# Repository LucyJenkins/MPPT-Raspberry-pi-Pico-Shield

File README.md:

# MPPT-Raspberry-pi-Pico-Shield
A small project implementing a Maximum Power Point Tracker using the format of Raspberry pi Pico Shield

# References:
1. https://fr.scribd.com/document/404356941/Regulated-Output-Voltage-Double-Switch-Buck-Boost-Converter-for-Photovoltaic-Energy-Application 
2. https://www.engr.colostate.edu/ECE562/98lectures/l09.pdf

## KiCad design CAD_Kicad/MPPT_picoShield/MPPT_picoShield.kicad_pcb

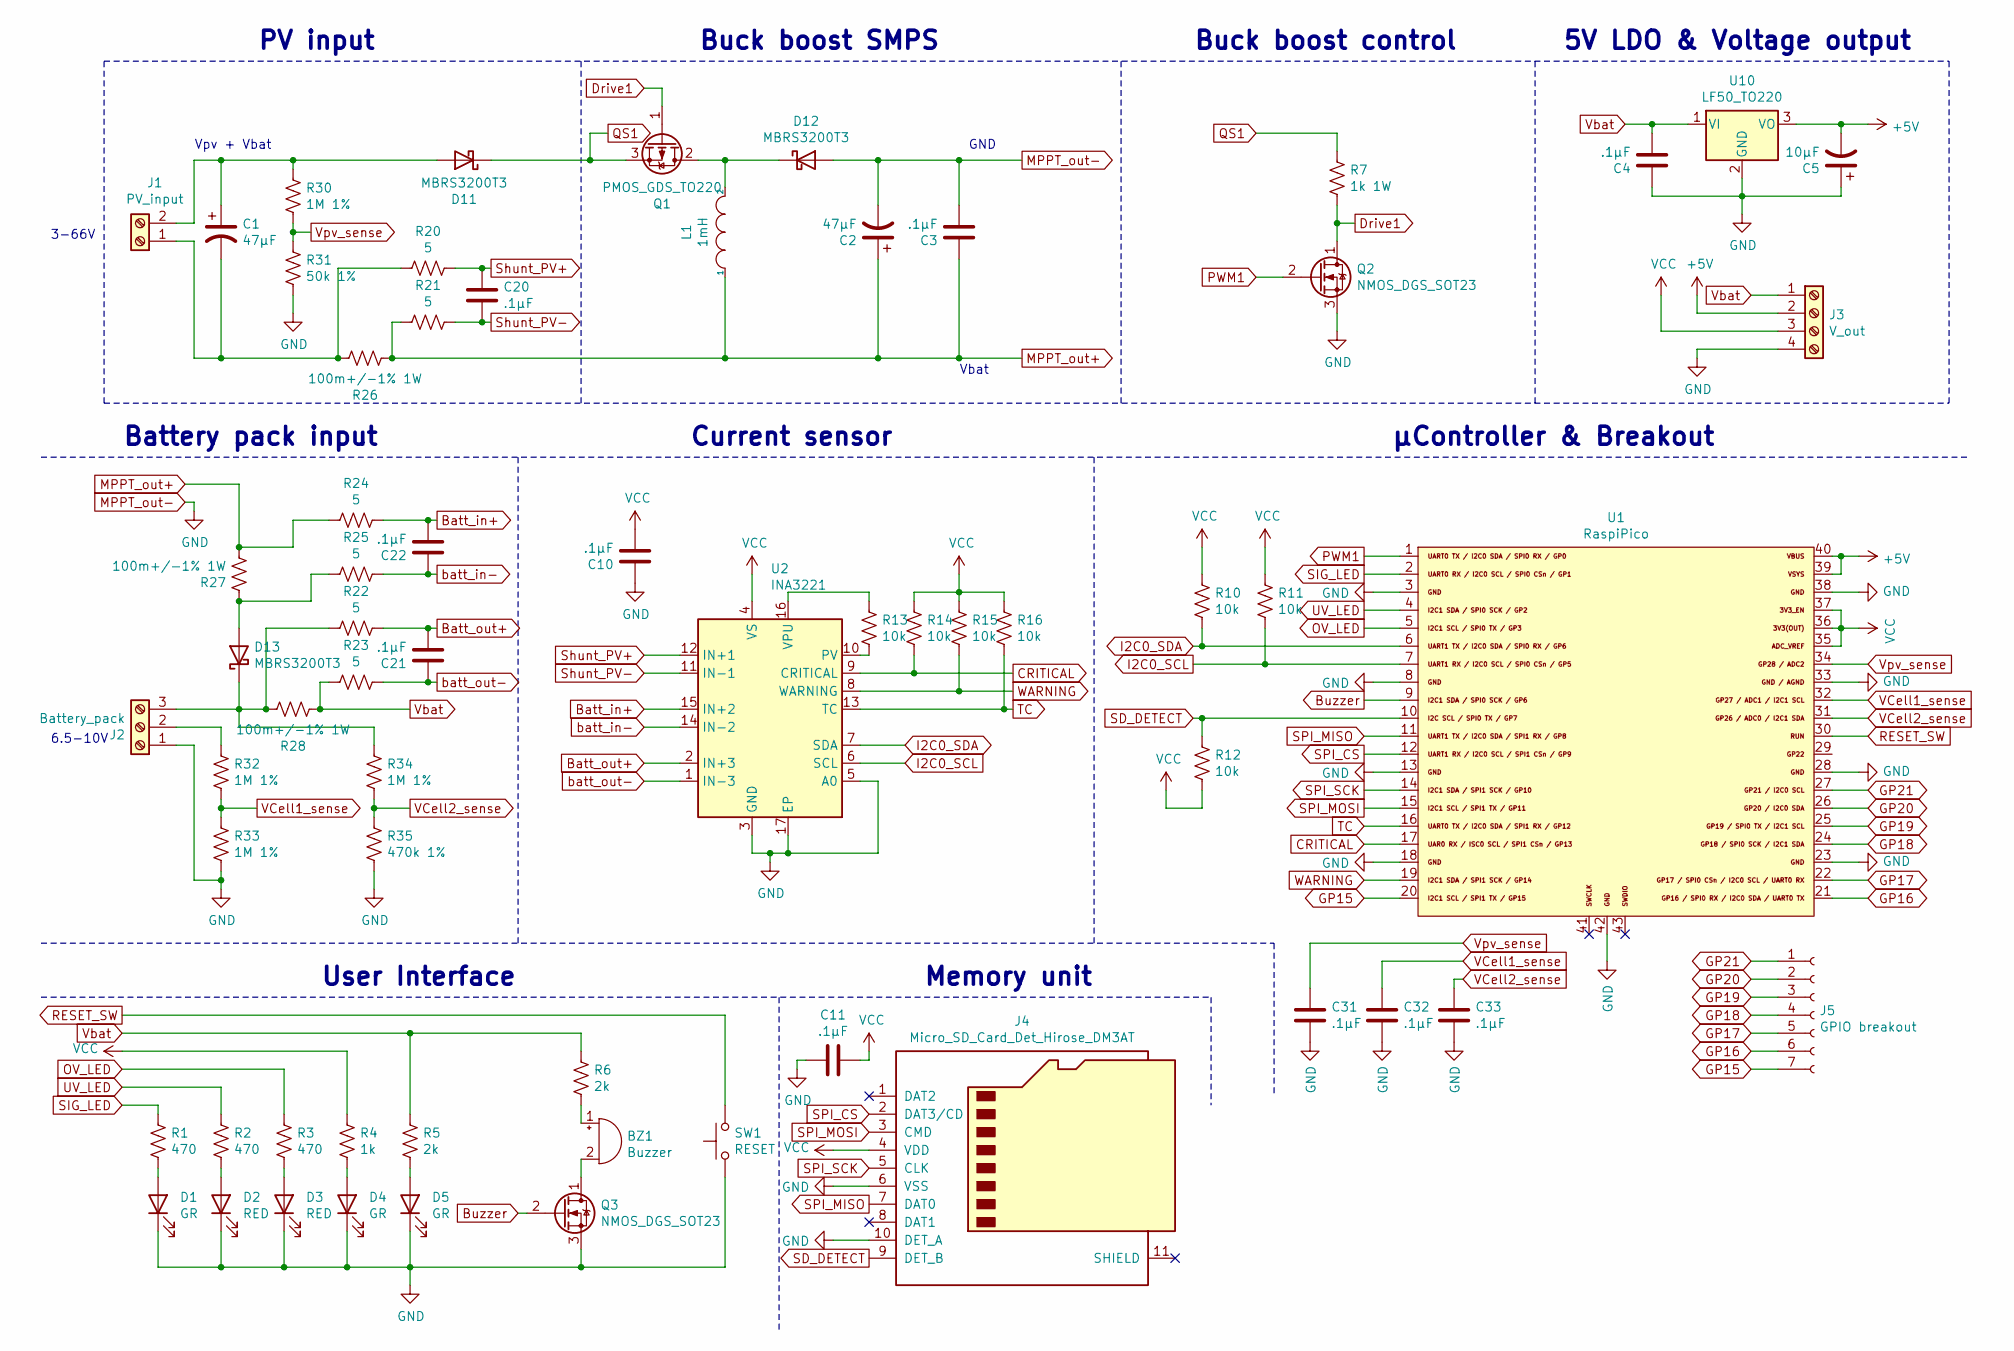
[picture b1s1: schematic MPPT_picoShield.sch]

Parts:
BZ1: Buzzer; PKM13EPYH4002-B0
C1, C2: 47µF; CP_Radial_D10.0mm_P5.00mm
C3, C4, C10, C11, C20, C21, C22, C31, C32, C33: .1µF; C_0603_1608Metric
C5: 10µF; CP_Radial_D10.0mm_P5.00mm
D1, D4, D5: GR; LED_0805_2012Metric
D2, D3: RED; LED_0805_2012Metric
D11, D12, D13: MBRS3200T3; MBRS3200T3G
J1: PV_input; TerminalBlock_bornier-2_P5.08mm
J2: Battery_pack; TerminalBlock_bornier-3_P5.08mm
J3: V_out; TerminalBlock_bornier-4_P5.08mm
J4: Micro_SD_Card_Det_Hirose_DM3AT; DM3ATSFPEJM5
J5: GPIO breakout; PinHeader_1x07_P2.54mm_Vertical
L1: 1mH; PA4320.105NLT
Q1: PMOS_GDS_TO220; TO-220-3_Vertical
Q2, Q3: NMOS_DGS_SOT23; SOT-23
R1, R2, R3: 470; R_0603_1608Metric
R4: 1k; R_0603_1608Metric
R5, R6: 2k; R_0603_1608Metric
R7: 1k 1W; R_1206_3216Metric
R10, R11, R12, R13, R14, R15, R16: 10k; R_0603_1608Metric
R20, R21, R22, R23, R24, R25: 5; R_0603_1608Metric
R26, R27, R28: 100m+/-1% 1W; R_1206_3216Metric
R30, R32, R33, R34: 1M 1%; R_0603_1608Metric
R31: 50k 1%; R_0603_1608Metric
R35: 470k 1%; R_0603_1608Metric
SW1: RESET; SW_PUSH_6mm
U1: RaspiPico
U2: INA3221; Texas_RGV_S-PVQFN-N16_EP2.1x2.1mm
U10: LF50_TO220; TO-220-3_Vertical

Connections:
+5V: C5.2, J3.2, U1.39, U1.40, U10.3 (VO)
Batt_in+: C22.2, R24.1, U2.15 (IN+2)
Batt_out+: C21.2, R22.1, U2.2 (IN+3)
Buzzer: Q3.2 (G), U1.9
CRITICAL: R14.2, U1.17, U2.9 (CRITICAL)
Drive1: Q1.1 (G), Q2.1 (D), R7.2
GP15: J5.7, U1.20
GP16: J5.6, U1.21
GP17: J5.5, U1.22
GP18: J5.4, U1.24
GP19: J5.3, U1.25
GP20: J5.2, U1.26
GP21: J5.1, U1.27
I2C0_SCL: R11.2, U1.7, U2.6 (SCL)
I2C0_SDA: R10.2, U1.6, U2.7 (SDA)
MPPT_out+: C2.1, C3.1, L1.1, R21.2, R24.2, R26.2, R27.2; also elsewhere on the board
MPPT_out-: C2.2, C3.2, C4.1, C5.1, C10.1, C11.2, C31.2, C32.2, C33.2, D1.1 (K), D2.1 (K), D3.1 (K), D4.1 (K), D5.1 (K), D12.2 (A), J2.1, J3.4, J4.6 (VSS), J4.10 (DET_A), Q2.3 (S), Q3.3 (S), R31.2, R33.2, R35.2, SW1.1, U1.3, U1.8, U1.13, U1.18, U1.23, U1.28, U1.33, U1.38, U1.42, U2.3 (GND), U2.5 (A0), U2.17 (EP), U10.2 (GND); also elsewhere on the board
unnamed: BZ1.1 (-), R6.2
unnamed: BZ1.2 (+), Q3.1 (D)
unnamed 19: C1.1, D11.2 (A), J1.2, R30.1; also elsewhere on the board
unnamed 20: C1.2, J1.1, R20.2, R26.1; also elsewhere on the board
unnamed: D1.2 (A), R1.2
unnamed: D2.2 (A), R2.2
unnamed: D3.2 (A), R3.2
unnamed: D4.2 (A), R4.2
unnamed: D5.2 (A), R5.2
unnamed 26: D12.1 (K), L1.2, Q1.2 (D); also elsewhere on the board
unnamed: D13.1 (K), J2.3, R22.2, R28.1, R34.1
unnamed: D13.2 (A), R25.2, R27.1
unnamed: J2.2, R32.1
unnamed: R13.1, U2.16 (VPU)
unnamed: R13.2, U2.10 (PV)
OV_LED: R3.1, U1.5
PWM1: Q2.2 (G), U1.1
QS1: D11.1 (K), Q1.3 (S), R7.1
RESET_SW: SW1.2, U1.30
SD_DETECT: J4.9 (DET_B), R12.1, U1.10
SIG_LED: R1.1, U1.2
SPI_CS: J4.2 (DAT3/CD), U1.12
SPI_MISO: J4.7 (DAT0), U1.11
SPI_MOSI: J4.3 (CMD), U1.15
SPI_SCK: J4.5 (CLK), U1.14
Shunt_PV+: C20.1, R20.1, U2.12 (IN+1)
Shunt_PV-: C20.2, R21.1, U2.11 (IN-1)
TC: R16.2, U1.16, U2.13 (TC)
UV_LED: R2.1, U1.4
VCC: C10.2, C11.1, J3.3, J4.4 (VDD), R4.1, R10.1, R11.1, R12.2, R14.1, R15.1, R16.1, U1.35, U1.36, U1.37, U2.4 (VS); also elsewhere on the board
VCell1_sense: C32.1, R32.2, R33.1, U1.32
VCell2_sense: C33.1, R34.2, R35.1, U1.31
Vbat: C4.2, J3.1, R5.1, R6.1, R23.2, R28.2, U10.1 (VI); also elsewhere on the board
Vpv_sense: C31.1, R30.2, R31.1, U1.34
WARNING: R15.2, U1.19, U2.8 (WARNING)
batt_in-: C22.1, R25.1, U2.14 (IN-2)
batt_out-: C21.1, R23.1, U2.1 (IN-3)

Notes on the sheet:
Vpv + Vbat
Vbat
GND
Buck boost SMPS
PV input
Battery pack input
Buck boost control
µController & Breakout
User Interface
Memory unit
5V LDO & Voltage output
Current sensor
3-66V
6.5-10V

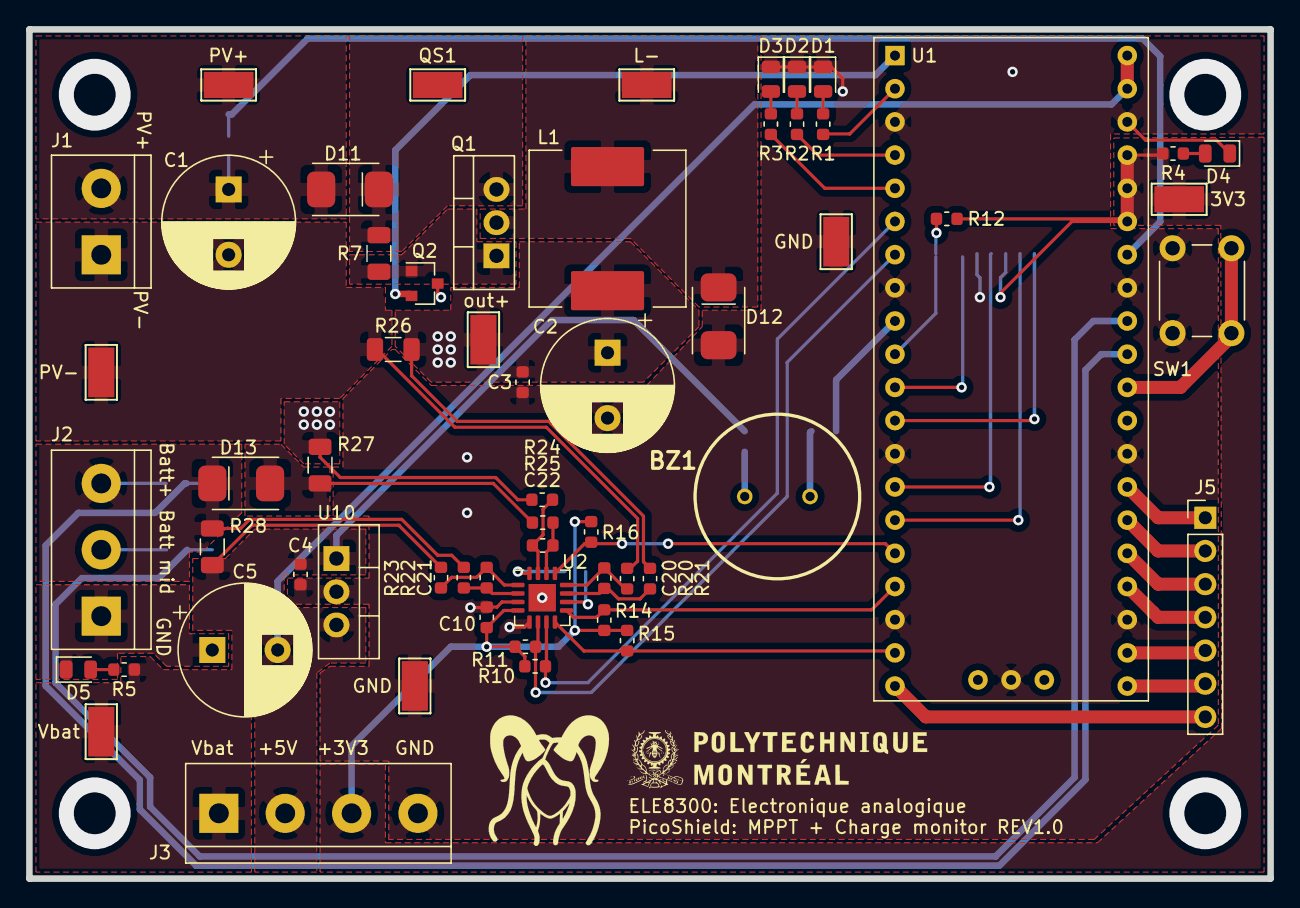
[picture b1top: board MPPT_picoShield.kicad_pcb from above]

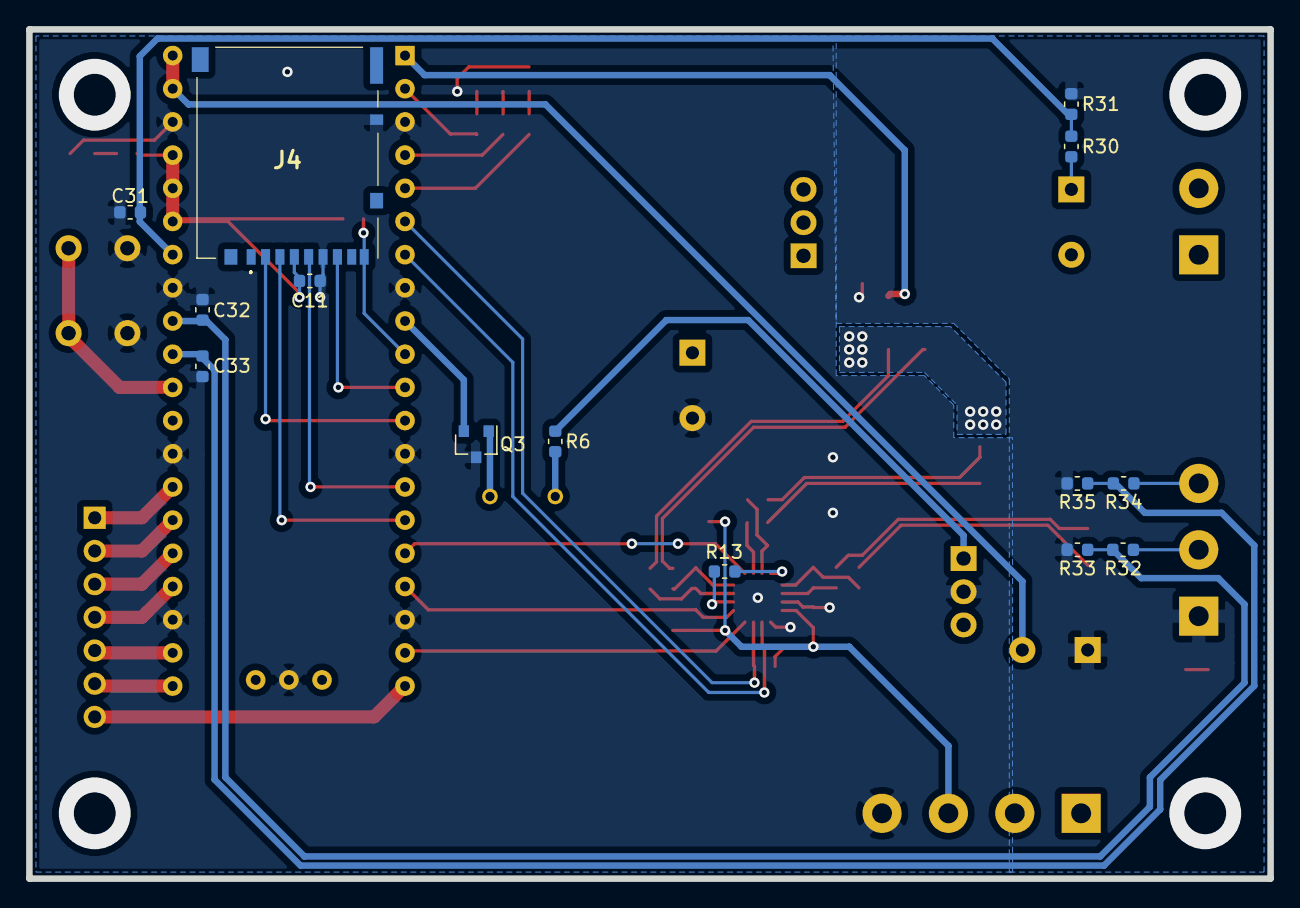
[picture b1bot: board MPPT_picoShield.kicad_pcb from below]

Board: 2 copper layers, 95.0 x 65.0 mm, 73 parts (14 on the bottom side), 54 nets.

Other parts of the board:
3V3: TestPoint_Keystone_5019_Minature
GND: TestPoint_Keystone_5019_Minature
GND#2: TestPoint_Keystone_5019_Minature
L-: TestPoint_Keystone_5019_Minature
PV+: TestPoint_Keystone_5019_Minature
PV-: TestPoint_Keystone_5019_Minature
QS1: TestPoint_Keystone_5019_Minature
Vbat: TestPoint_Keystone_5019_Minature
out+: TestPoint_Keystone_5019_Minature

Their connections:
MPPT_out+: out+.1; also elsewhere on the board
MPPT_out-: GND.1, GND#2.1; also elsewhere on the board
unnamed 19: PV+.1; also elsewhere on the board
unnamed 20: PV-.1; also elsewhere on the board
unnamed 26: L-.1; also elsewhere on the board
VCC: 3V3.1; also elsewhere on the board
Vbat: Vbat.1; also elsewhere on the board

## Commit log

2022-03-15 Add files via upload
    Initial commit of hardware schematic - basic architecture layed - has to be finished
2022-03-16 Finished electrical schematic - pending review
    Final decisions on component choices have to be made, special attention should be put towards the microSD card (there seems to be a conflict between electrical schematic and footprint gathered on the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
2022-03-17 Initial placement of components on PCB board
    Initial placement - issue spotted on shunt resistors: hard to route because of crossing, pending solution
2022-03-18 Initial routing
    Small verifications to be made:
    - Should Metal of INA2331 be connected to ground? Or a floating metal plane? or Vcc?
    - Should capacitors be added to the long analog lines to stabilize them?
    - Should D11 and its polarized cap be swapped to "idiot proof" the PV connector?
    - Rasp Pico silkscreen is outside of PCB, should probably fix that
    - Indicator of pin 1 on INA2331 is overlapping a via, small esthetic fix to be made
2022-03-23 Small Changes for hardware "correctability" reasons
    Added testpoints
    Changed rooting around INA to solve the thermal pad to ground uncertainty. Now able to solve this using an exacto blade
    Added PolyMTL logo
2022-03-23 Gerber gen and added filtering caps on ADC lines
2022-04-07 Basic system logic and on-computer simulation
2022-04-07 Logic and sim update
    Fixed python grammar issue
    Added logic to search a working power point if no power is seen (cycle through all duty cycles with a ramp until a working point can be found)
    Updated simulation logic to allow for tracking tests using a sinusoidal power on solar panel. Updated simulation logic to prevent negative current generation (exponent of exponential greater than 0)
2022-04-08 Logic refactor and improvement
    Target of the application is to charge a battery => The input current of the battery pack is the most important variable of the system. We thus try to follow the desired intensity with the buck boost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
    Pending further readability improvements (may delete unused sections)
2022-04-11 Logic & sim feedback improvements
    Logic improvements include:
    - mapping of available currents to quickly converge to a solution (tries to mitigate the local maximum problem)
    Sim improvements include:
    - brute forcing for the best solution at every simulation point
    - ouput of those point in the .csv output of the script
    Readability improvements include
